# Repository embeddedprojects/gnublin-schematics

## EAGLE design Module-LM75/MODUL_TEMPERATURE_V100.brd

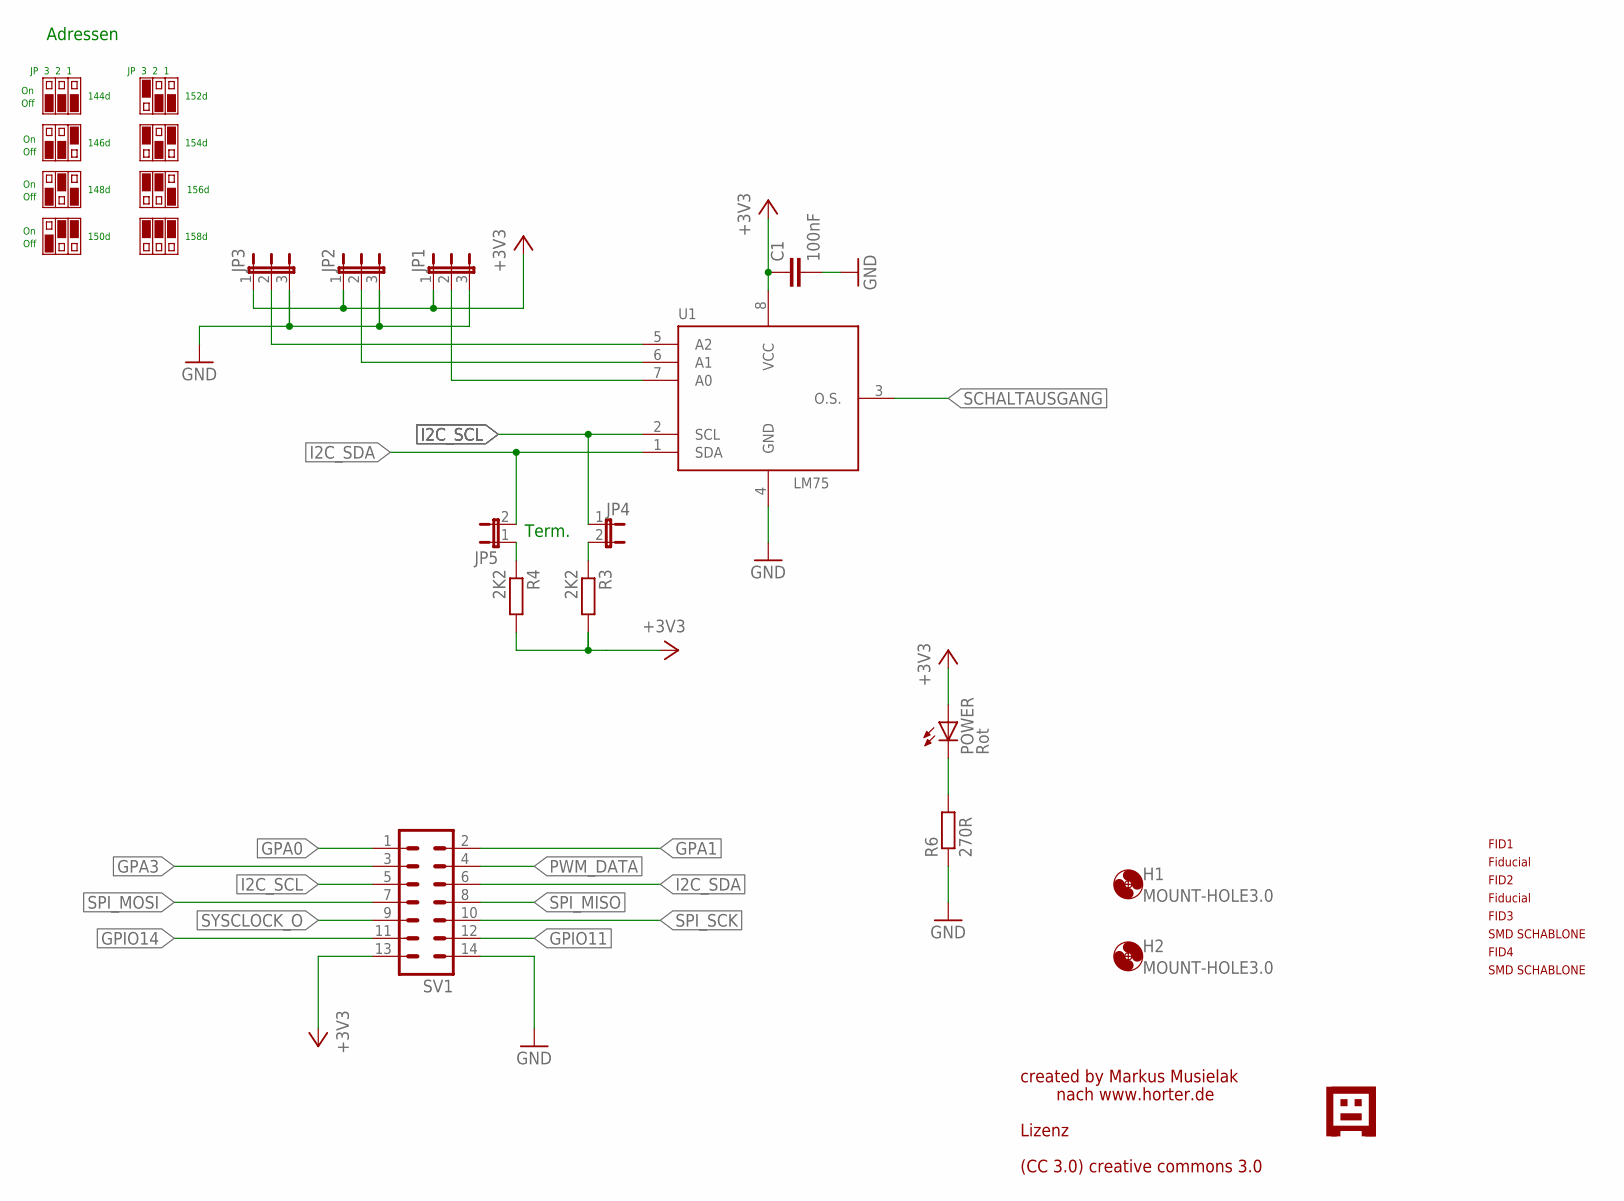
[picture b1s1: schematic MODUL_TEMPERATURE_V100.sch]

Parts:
C1: 100nF; C0805
FID1, FID2, FID3, FID4: PASSERMARKEN_FIDUCIAL
H1, H2: MOUNT-HOLE3.0; 3,0
JP1, JP2, JP3: JP2E; JP2
JP4, JP5: JP1E; JP1
POWER: Rot; CHIP-LED0805
R3, R4: 2K2; R0805
R6: 270R; R0805
SV1: ML14
U1: LM75; SO-8; FARNELL 1699380
U$1: GNUBLINLOGOSIEB; GNUSIEBDRUCK

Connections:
+3V3: C1.1, JP1.1, JP2.1, JP3.1, POWER.A, R3.2, R4.2, SV1.13, U1.8 (VCC)
GND: C1.2, JP1.3, JP2.3, JP3.3, R6.1, SV1.14, U1.4 (GND)
GPA0: SV1.1
GPA1: SV1.2
GPA3: SV1.3
GPIO11: SV1.12
GPIO14: SV1.11
I2C_SCL: JP4.1, SV1.5, U1.2 (SCL)
I2C_SDA: JP5.2, SV1.6, U1.1 (SDA)
unnamed: JP1.2, U1.7 (A0)
unnamed: JP2.2, U1.6 (A1)
unnamed: JP3.2, U1.5 (A2)
unnamed: JP4.2, R3.1
unnamed: JP5.1, R4.1
unnamed: POWER.C, R6.2
PWM_DATA: SV1.4
SCHALTAUSGANG: U1.3 (O.S.)
SPI_MISO: SV1.8
SPI_MOSI: SV1.7
SPI_SCK: SV1.10
SYSCLOCK_O: SV1.9

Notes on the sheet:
Term.
nach www.horter.de
Adressen
JP 3 2 1
Off
144d
146d
148d
150d
152d
154d
156d
158d
created by Markus Musielak
Lizenz
(CC 3.0) creative commons 3.0

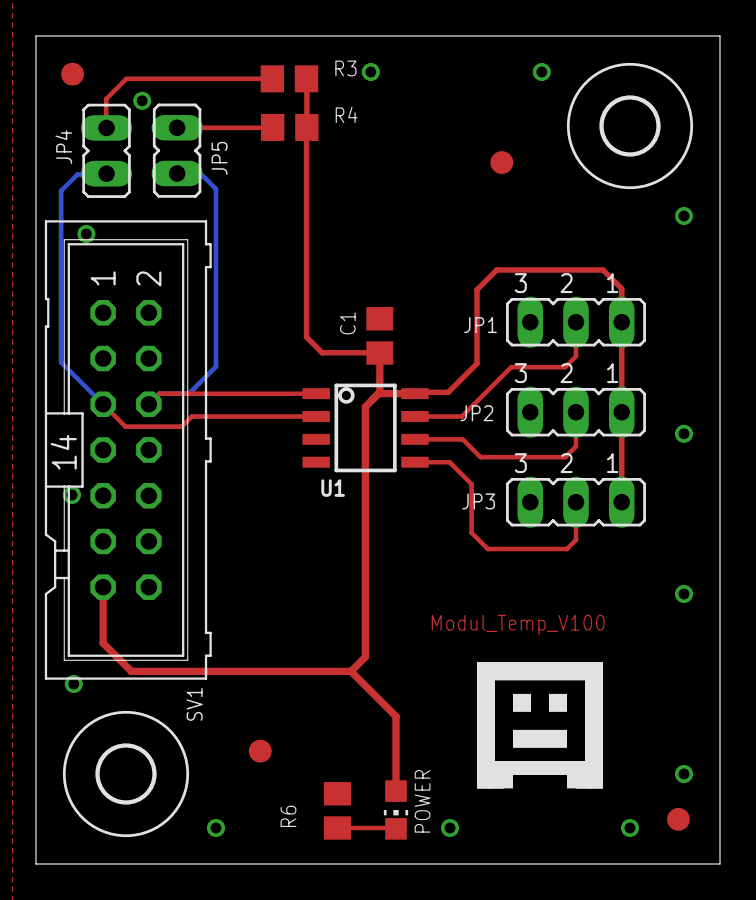
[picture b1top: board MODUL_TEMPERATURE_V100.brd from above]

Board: 2 copper layers, 38.0 x 46.0 mm, 19 parts (0 on the bottom side), 10 nets.

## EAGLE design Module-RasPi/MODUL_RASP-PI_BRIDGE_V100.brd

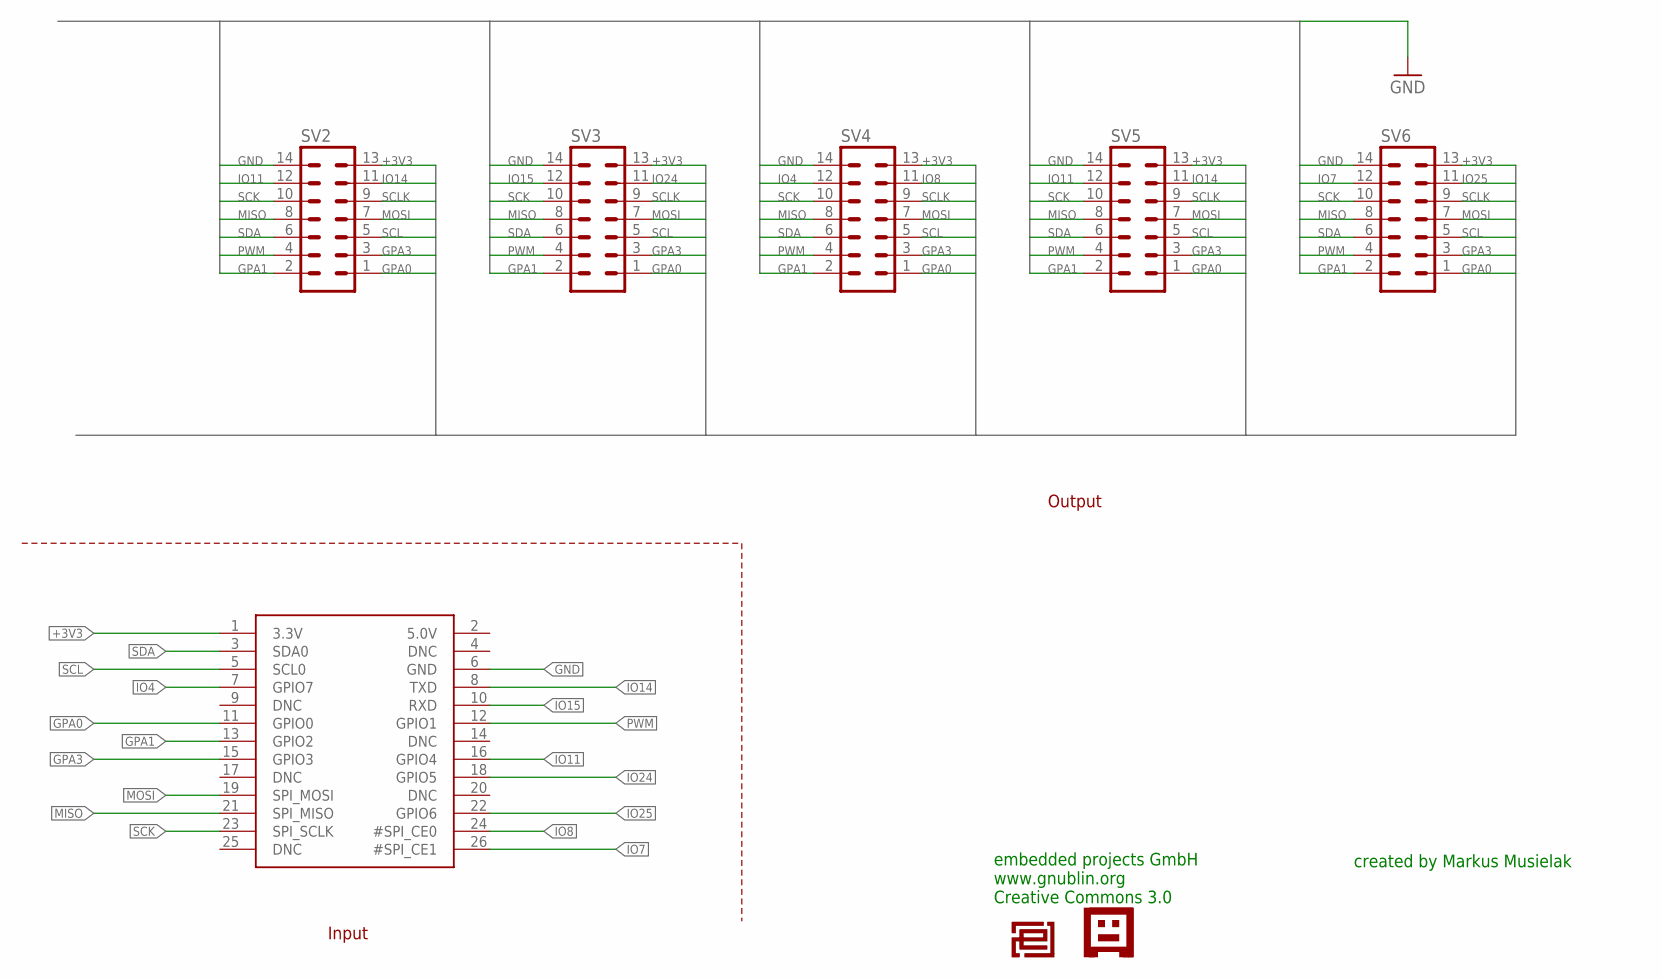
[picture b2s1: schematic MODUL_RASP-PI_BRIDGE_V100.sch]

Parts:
SV2, SV3, SV4, SV5, SV6: ML14
U$1: RASPBERRYPI_BB; RASBERRYPI_SHIELD
U$2: EPLOGOSIEB; EPLOGOSIEBDRUCK
U$4: GNUBLINLOGOSIEB; GNUSIEBDRUCK

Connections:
+3V3: SV2.13, SV3.13, SV4.13, SV5.13, SV6.13, U$1.1 (3.3V)
GND: SV2.14, SV3.14, SV4.14, SV5.14, SV6.14, U$1.6 (GND)
GPA0: SV2.1, SV3.1, SV4.1, SV5.1, SV6.1, U$1.11 (GPIO0)
GPA1: SV2.2, SV3.2, SV4.2, SV5.2, SV6.2, U$1.13 (GPIO2)
GPA3: SV2.3, SV3.3, SV4.3, SV5.3, SV6.3, U$1.15 (GPIO3)
IO4: SV4.12, U$1.7 (GPIO7)
IO7: SV6.12, U$1.26 (#SPI_CE1)
IO8: SV4.11, U$1.24 (#SPI_CE0)
IO11: SV2.12, SV5.12, U$1.16 (GPIO4)
IO14: SV2.11, SV5.11, U$1.8 (TXD)
IO15: SV3.12, U$1.10 (RXD)
IO24: SV3.11, U$1.18 (GPIO5)
IO25: SV6.11, U$1.22 (GPIO6)
MISO: SV2.8, SV3.8, SV4.8, SV5.8, SV6.8, U$1.21 (SPI_MISO)
MOSI: SV2.7, SV3.7, SV4.7, SV5.7, SV6.7, U$1.19 (SPI_MOSI)
PWM: SV2.4, SV3.4, SV4.4, SV5.4, SV6.4, U$1.12 (GPIO1)
SCK: SV2.10, SV3.10, SV4.10, SV5.10, SV6.10, U$1.23 (SPI_SCLK)
SCL: SV2.5, SV3.5, SV4.5, SV5.5, SV6.5, U$1.5 (SCL0)
SCLK: SV2.9, SV3.9, SV4.9, SV5.9, SV6.9
SDA: SV2.6, SV3.6, SV4.6, SV5.6, SV6.6, U$1.3 (SDA0)

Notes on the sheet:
created by Markus Musielak
Input
Output
embedded projects GmbH www.gnublin.org Creative Commons 3.0

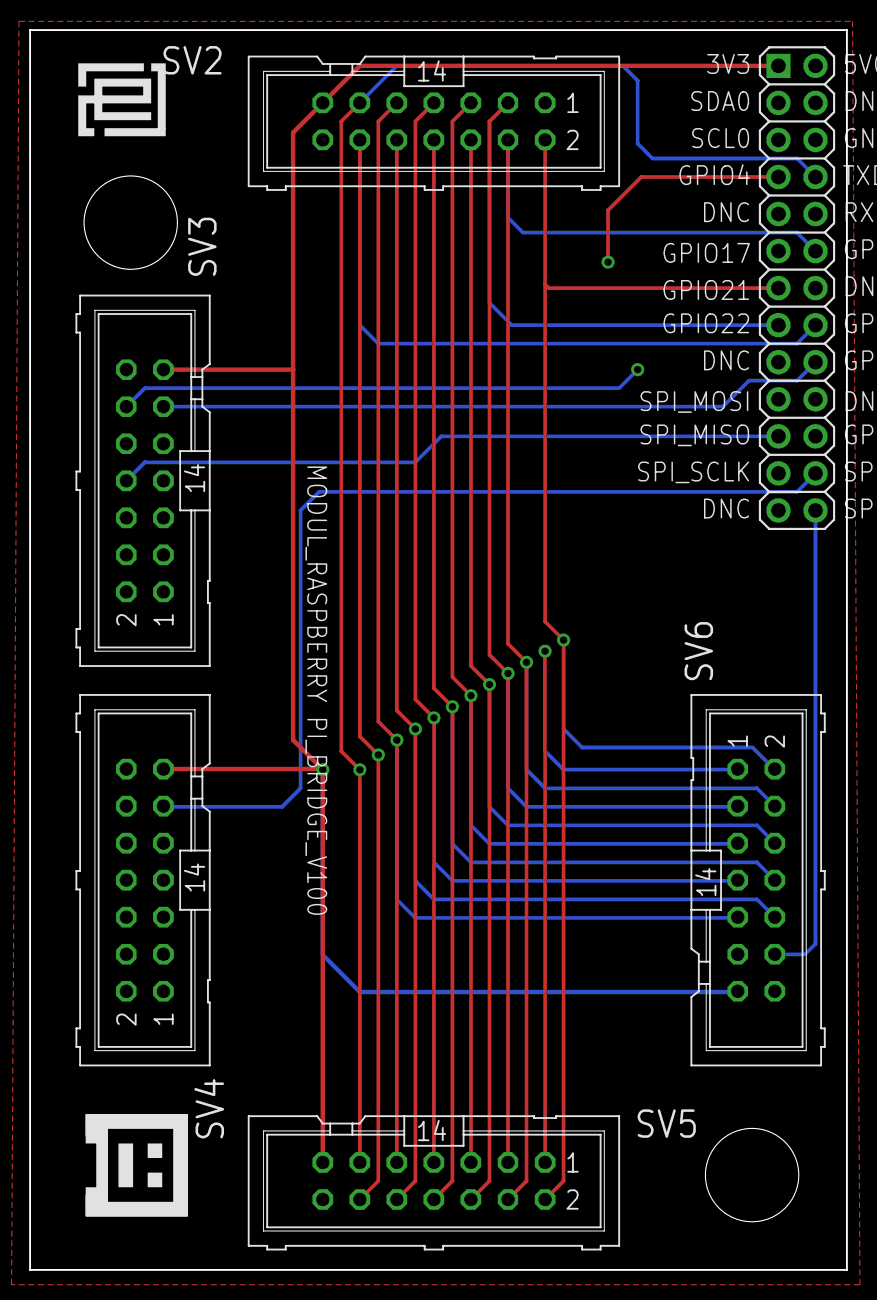
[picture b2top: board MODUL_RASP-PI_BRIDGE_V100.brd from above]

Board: 4 copper layers, 56.0 x 85.0 mm, 8 parts (0 on the bottom side), 20 nets.

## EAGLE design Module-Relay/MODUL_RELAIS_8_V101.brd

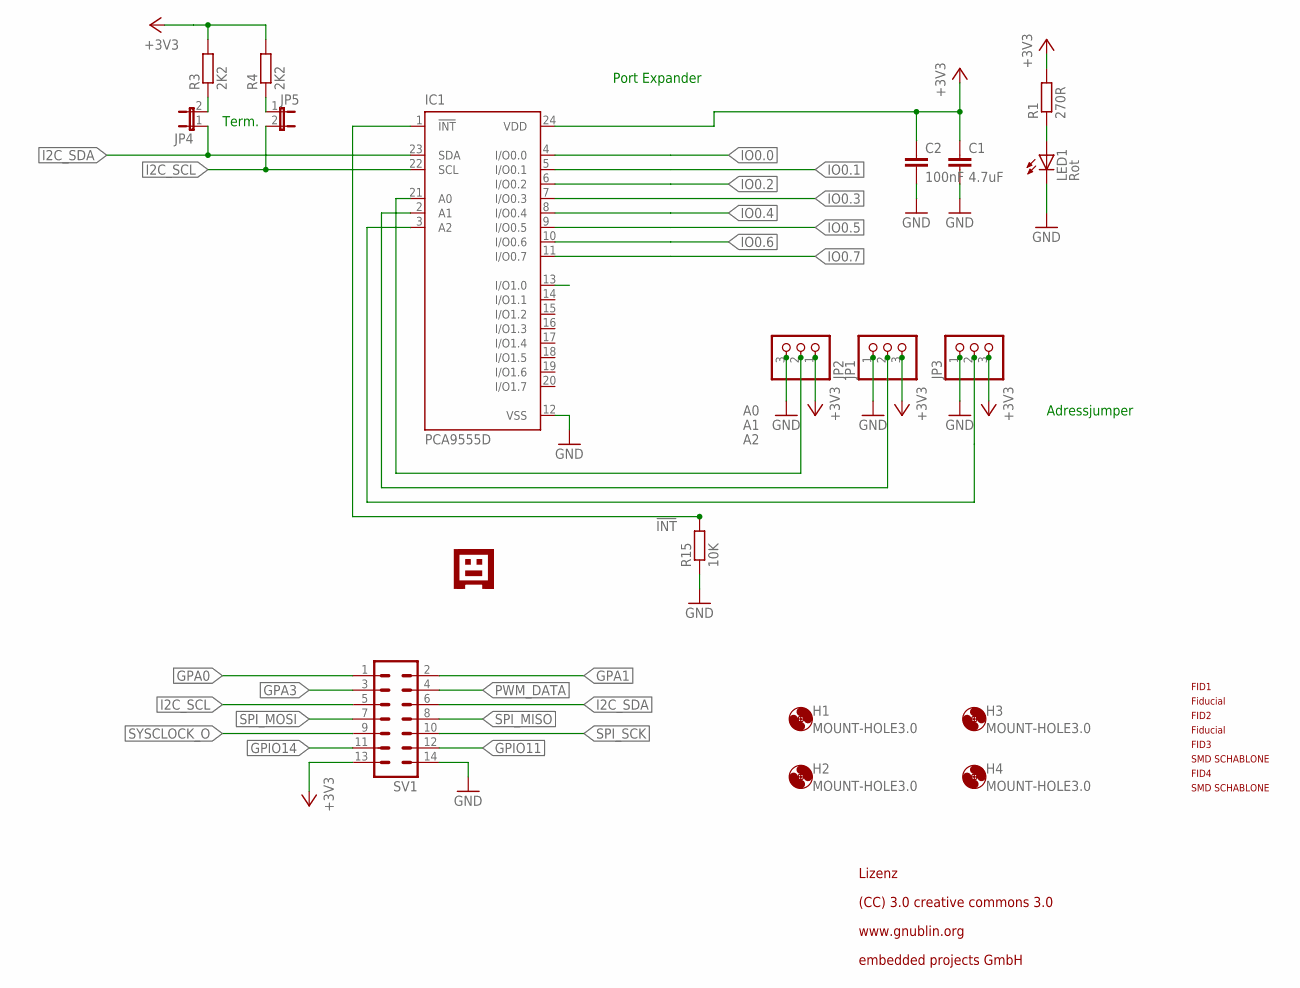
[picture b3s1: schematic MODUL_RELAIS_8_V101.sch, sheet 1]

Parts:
C1: 4.7uF; C0805
C2: 100nF; C0805
FID1, FID2, FID3, FID4: PASSERMARKEN_FIDUCIAL
H1, H2, H3, H4: MOUNT-HOLE3.0; 3,0
IC1: PCA9555D; SO24
JP1, JP2, JP3: PINHD-1X3; 1X03
JP4, JP5: JP1E; JP1
LED1: Rot; CHIP-LED0805
R1: 270R; R0805
R3, R4: 2K2; R0805
R15: 10K; R0805
SV1: ML14
U$1: GNUBLINLOGOSIEB; GNUSIEBDRUCK

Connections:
!INT: IC1.1 (!INT), R15.2
+3V3: C1.1, C2.1, IC1.24 (VDD), JP1.3, JP2.1, JP3.3, R1.2, R3.2, R4.2, SV1.13; also elsewhere on the board
A0: IC1.21 (A0), JP2.2
A1: IC1.2 (A1), JP1.2
A2: IC1.3 (A2), JP3.2
GND: C1.2, C2.2, IC1.12 (VSS), JP1.1, JP2.3, JP3.1, LED1.C, R15.1, SV1.14; also elsewhere on the board
GPA0: SV1.1
GPA1: SV1.2
GPA3: SV1.3
GPIO11: SV1.12
GPIO14: SV1.11
I2C_SCL: IC1.22 (SCL), JP5.2, SV1.5
I2C_SDA: IC1.23 (SDA), JP4.1, SV1.6
IO0.0: IC1.4 (I/O0.0); also elsewhere on the board
IO0.1: IC1.5 (I/O0.1); also elsewhere on the board
IO0.2: IC1.6 (I/O0.2); also elsewhere on the board
IO0.3: IC1.7 (I/O0.3); also elsewhere on the board
IO0.4: IC1.8 (I/O0.4); also elsewhere on the board
IO0.5: IC1.9 (I/O0.5); also elsewhere on the board
IO0.6: IC1.10 (I/O0.6); also elsewhere on the board
IO0.7: IC1.11 (I/O0.7); also elsewhere on the board
IO1.0: IC1.13 (I/O1.0)
unnamed: JP4.2, R3.1
unnamed: LED1.A, R1.1
unnamed: JP5.1, R4.1
PWM_DATA: SV1.4
SPI_MISO: SV1.8
SPI_MOSI: SV1.7
SPI_SCK: SV1.10
SYSCLOCK_O: SV1.9

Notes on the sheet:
Port Expander
Adressjumper
Term.
(CC) 3.0 creative commons 3.0
Lizenz
www.gnublin.org
embedded projects GmbH

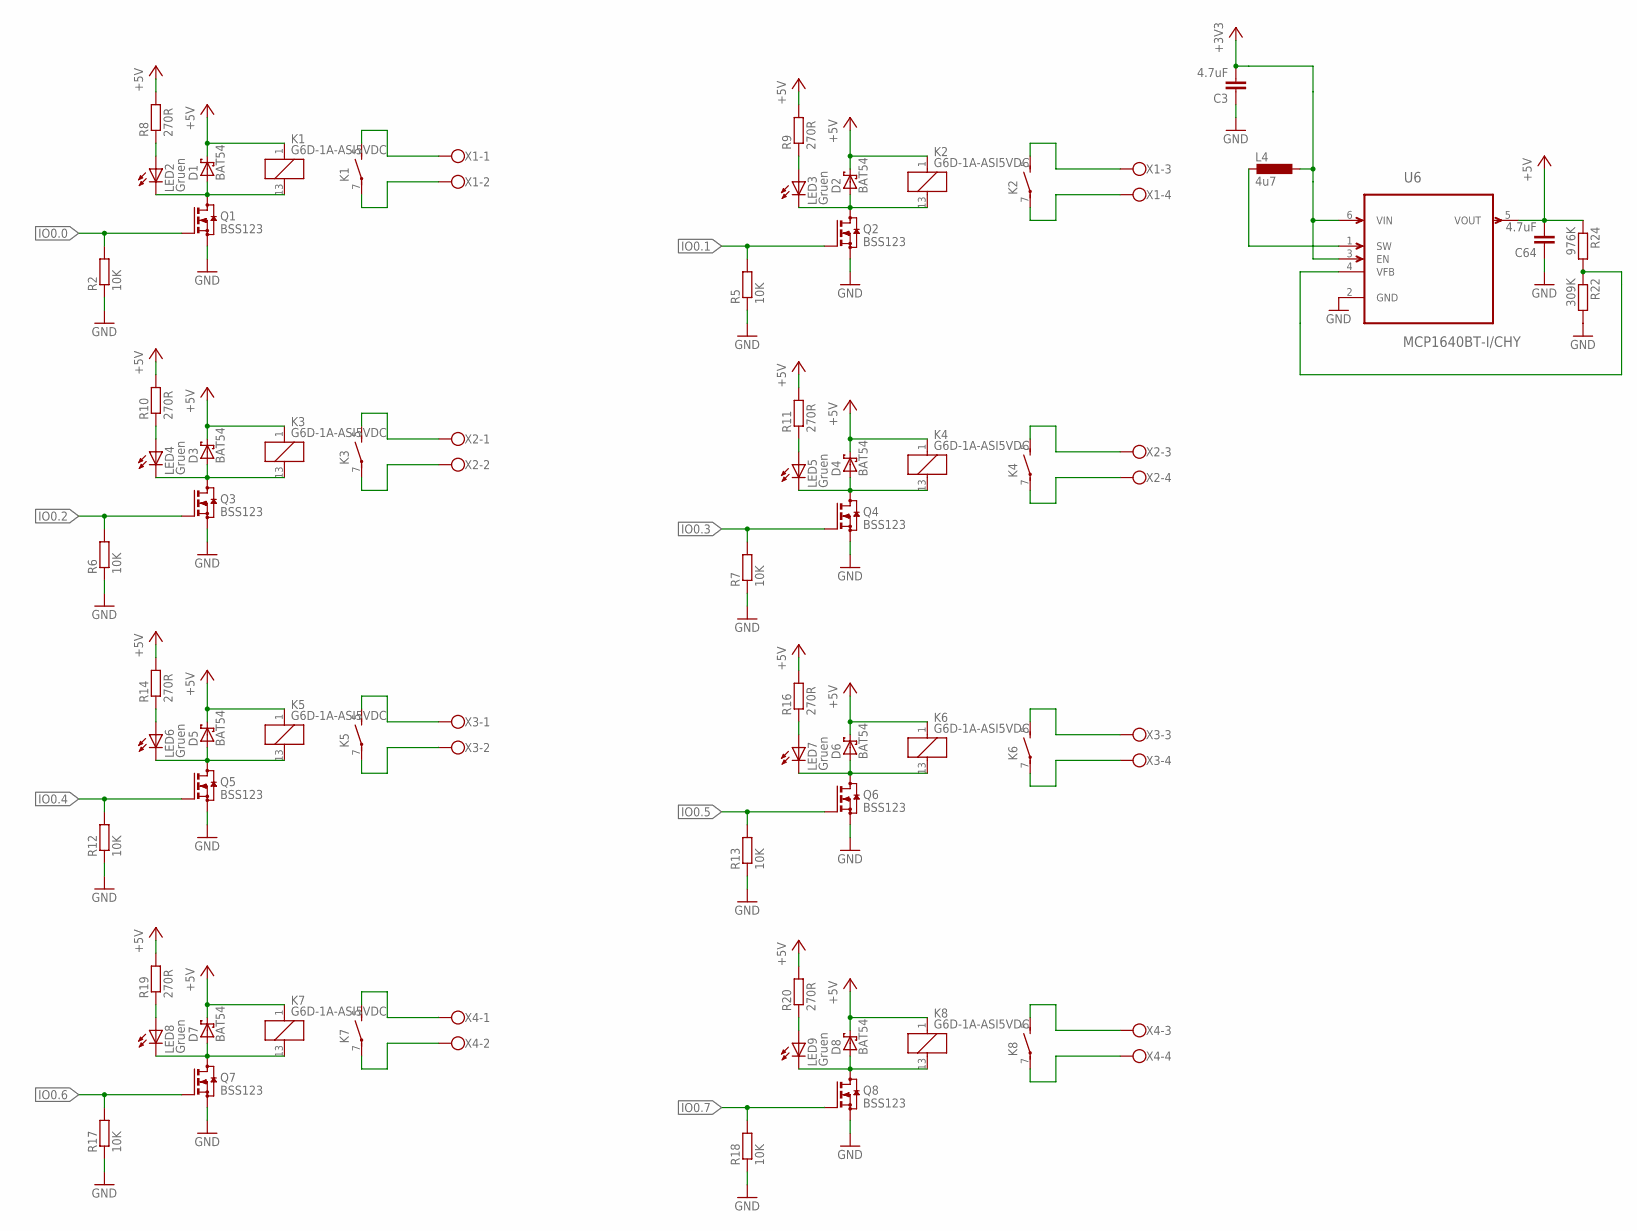
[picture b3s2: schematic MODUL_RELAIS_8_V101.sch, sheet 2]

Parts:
C3, C64: 4.7uF; C0805
D1, D2, D3, D4, D5, D6, D7, D8: BAT54; DIODE_SOT23
K1, K2, K3, K4, K5, K6, K7, K8: G6D-1A-ASI5VDC; RELAY_G6D
L4: 4u7; PSU3014
LED2, LED3, LED4, LED5, LED6, LED7, LED8, LED9: Gruen; CHIP-LED0805
Q1, Q2, Q3, Q4, Q5, Q6, Q7, Q8: BSS123; TRANSISTOR-SMALL-SIGNAL_SOT23
R2, R5, R6, R7, R12, R13, R17, R18: 10K; R0805
R8, R9, R10, R11, R14, R16, R19, R20: 270R; R0805
R22: 309K; R0805
R24: 976K; R0805
U6: MCP1640BT-I/CHY; SOT95P270X145-6N
X1, X2, X3, X4: W237-04P; W237-4P

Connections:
+3V3: C3.2, L4.2, U6.3 (EN), U6.6 (VIN); also elsewhere on the board
+5V: C64.2, D1.3 (C), D2.3 (C), D3.3 (C), D4.3 (C), D5.3 (C), D6.3 (C), D7.3 (C), D8.3 (C), K1.1, K2.1, K3.1, K4.1, K5.1, K6.1, K7.1, K8.1, R8.2, R9.2, R10.2, R11.2, R14.2, R16.2, R19.2, R20.2, R24.1, U6.5 (VOUT)
ENABLE_5V: L4.1, U6.1 (SW)
GND: C3.1, C64.1, Q1.2 (S), Q2.2 (S), Q3.2 (S), Q4.2 (S), Q5.2 (S), Q6.2 (S), Q7.2 (S), Q8.2 (S), R2.1, R5.1, R6.1, R7.1, R12.1, R13.1, R17.1, R18.1, R22.2, U6.2 (GND); also elsewhere on the board
IO0.0: Q1.1 (G), R2.2; also elsewhere on the board
IO0.1: Q2.1 (G), R5.2; also elsewhere on the board
IO0.2: Q3.1 (G), R6.2; also elsewhere on the board
IO0.3: Q4.1 (G), R7.2; also elsewhere on the board
IO0.4: Q5.1 (G), R12.2; also elsewhere on the board
IO0.5: Q6.1 (G), R13.2; also elsewhere on the board
IO0.6: Q7.1 (G), R17.2; also elsewhere on the board
IO0.7: Q8.1 (G), R18.2; also elsewhere on the board
unnamed: D1.1 (A), K1.13 (2), LED2.C, Q1.3 (D)
unnamed: LED2.A, R8.1
unnamed: D2.1 (A), K2.13 (2), LED3.C, Q2.3 (D)
unnamed: LED3.A, R9.1
unnamed: K1.5 (S), X1.1
unnamed: K1.7, X1.2
unnamed: K2.5 (S), X1.3
unnamed: K2.7, X1.4
unnamed: D3.1 (A), K3.13 (2), LED4.C, Q3.3 (D)
unnamed: D4.1 (A), K4.13 (2), LED5.C, Q4.3 (D)
unnamed: LED4.A, R10.1
unnamed: LED5.A, R11.1
unnamed: K3.5 (S), X2.1
unnamed: K3.7, X2.2
unnamed: K4.5 (S), X2.3
unnamed: K4.7, X2.4
unnamed: D5.1 (A), K5.13 (2), LED6.C, Q5.3 (D)
unnamed: D6.1 (A), K6.13 (2), LED7.C, Q6.3 (D)
unnamed: LED6.A, R14.1
unnamed: LED7.A, R16.1
unnamed: K5.5 (S), X3.1
unnamed: K5.7, X3.2
unnamed: K6.5 (S), X3.3
unnamed: K6.7, X3.4
unnamed: D7.1 (A), K7.13 (2), LED8.C, Q7.3 (D)
unnamed: D8.1 (A), K8.13 (2), LED9.C, Q8.3 (D)
unnamed: LED8.A, R19.1
unnamed: LED9.A, R20.1
unnamed: K7.5 (S), X4.1
unnamed: K7.7, X4.2
unnamed: K8.5 (S), X4.3
unnamed: K8.7, X4.4
unnamed: R22.1, R24.2, U6.4 (VFB)

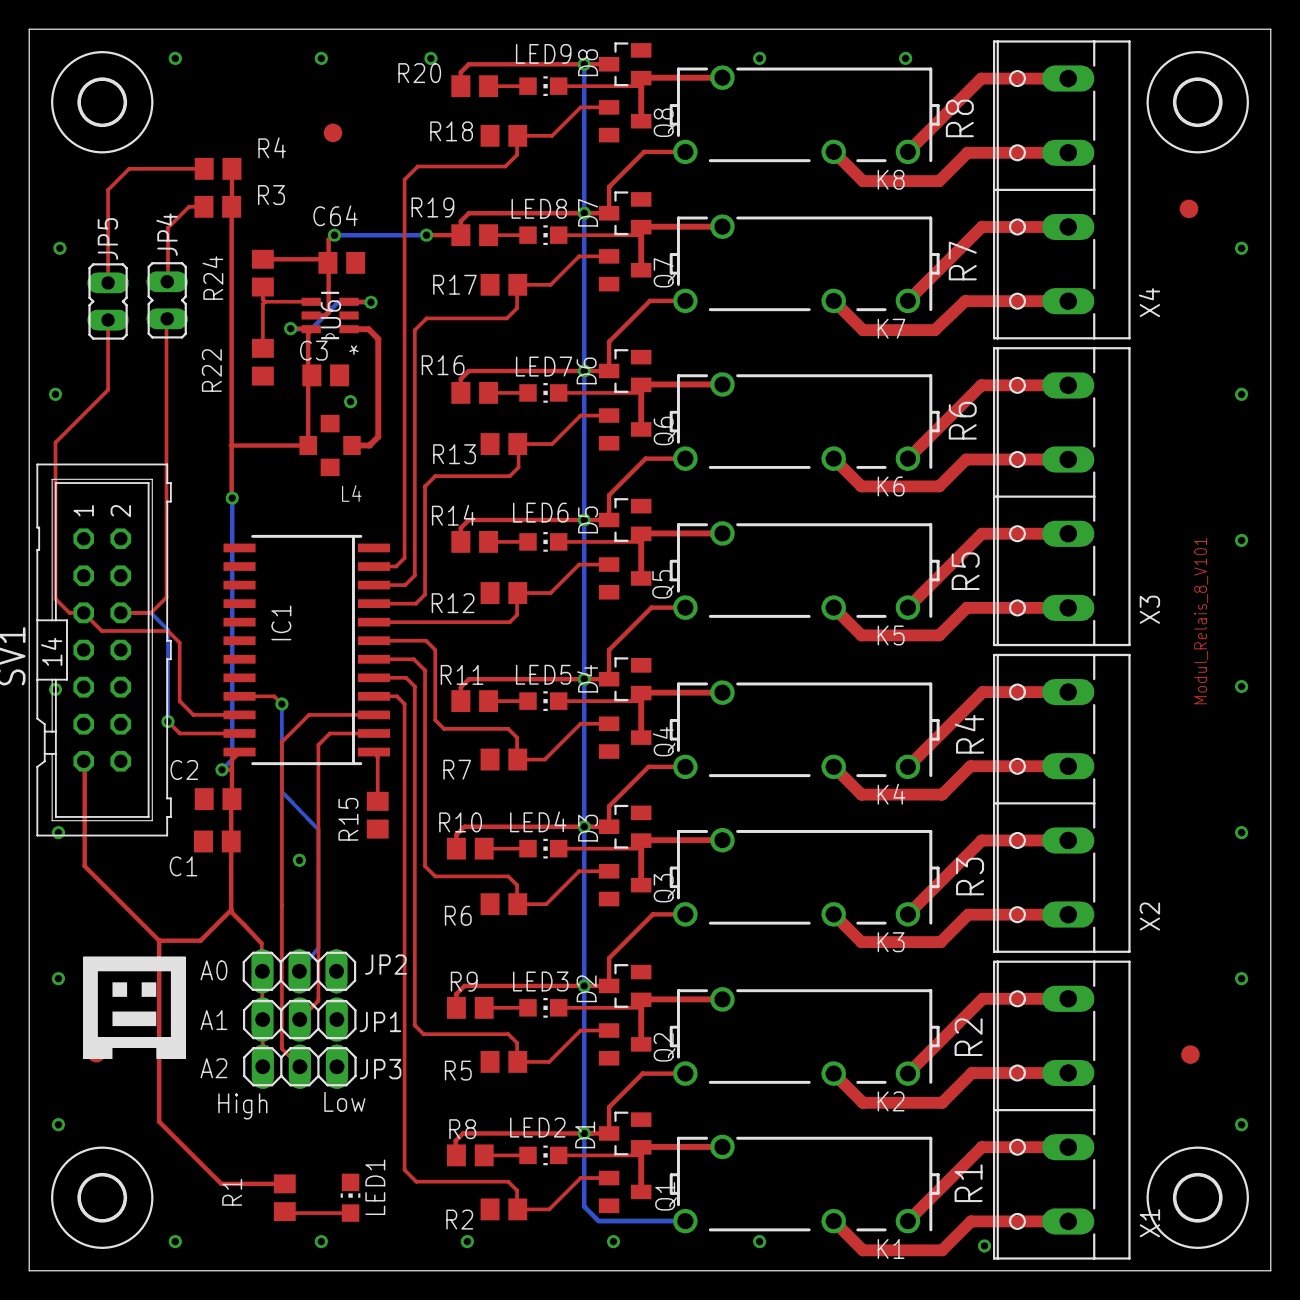
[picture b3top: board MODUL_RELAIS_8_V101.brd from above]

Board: 2 copper layers, 85.0 x 85.0 mm, 81 parts (0 on the bottom side), 54 nets.

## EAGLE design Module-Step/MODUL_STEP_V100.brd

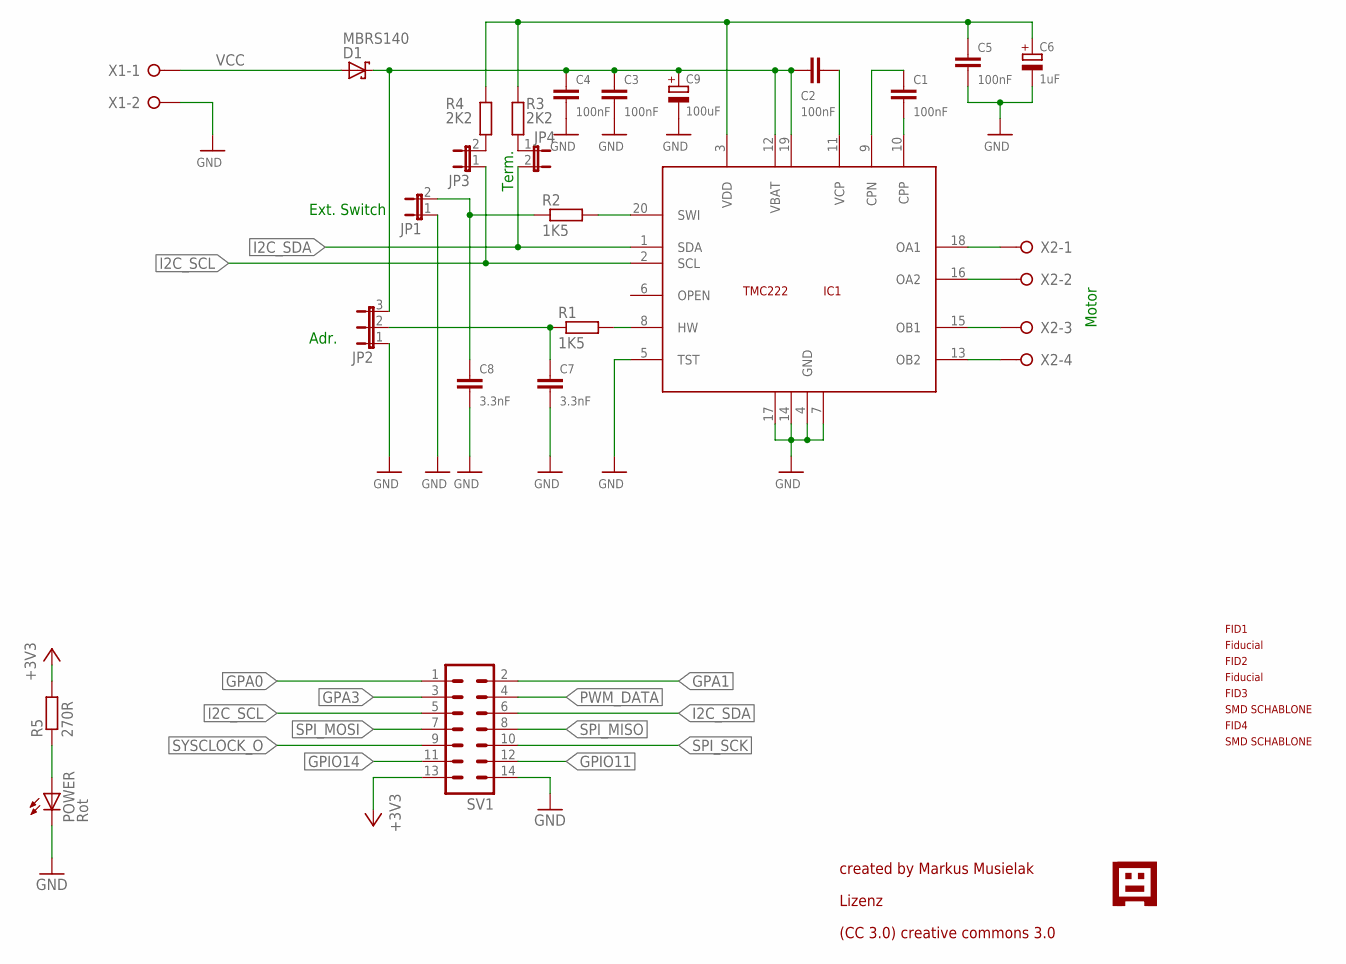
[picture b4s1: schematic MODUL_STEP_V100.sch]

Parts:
C1, C2, C3, C4, C5: 100nF; C0805
C6: 1uF; B/3528-21R
C7, C8: 3.3nF; C0805
C9: 100uF; E5-10,5
D1: MBRS140; SMB
FID1, FID2, FID3, FID4: PASSERMARKEN_FIDUCIAL
IC1: TMC222; SOIC20; FARNELL 1214195
JP1, JP3, JP4: JP1E; JP1
JP2: JP2E; JP2
POWER: Rot; CHIP-LED0805
R1, R2: 1K5; R0805
R3, R4: 2K2; R0805
R5: 270R; R0805
SV1: ML14
U$1: GNUBLINLOGOSIEB; GNUSIEBDRUCK
X1: W237-02P; W237-132
X2: W237-04P; W237-4P

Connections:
+3V3: R5.2, SV1.13
GND: C3.2, C4.2, C5.2, C6.-, C7.2, C8.2, C9.-, IC1.4 (GND), IC1.5 (TST), IC1.7 (GND2), IC1.14 (GND3), IC1.17 (GND4), JP1.1, JP2.1, POWER.C, SV1.14, X1.2
GPA0: SV1.1
GPA1: SV1.2
GPA3: SV1.3
GPIO11: SV1.12
GPIO14: SV1.11
I2C_SCL: IC1.2 (SCL), JP3.1, SV1.5
I2C_SDA: IC1.1 (SDA), JP4.2, SV1.6
unnamed: POWER.A, R5.1
unnamed: C1.1, IC1.9 (CPN)
unnamed: C1.2, IC1.10 (CPP)
unnamed: C2.2, IC1.11 (VCP)
unnamed: C2.1, C3.1, C4.1, C9.+, D1.C, IC1.12 (VBAT), IC1.19 (VBAT2), JP2.3
unnamed: IC1.8 (HW), R1.2
unnamed: C7.1, JP2.2, R1.1
unnamed: C8.1, JP1.2, R2.1
unnamed: IC1.20 (SWI), R2.2
unnamed: IC1.13 (OB2), X2.4
unnamed: IC1.15 (OB1), X2.3
unnamed: IC1.16 (OA2), X2.2
unnamed: IC1.18 (OA1), X2.1
unnamed: JP3.2, R4.1
unnamed: JP4.1, R3.1
unnamed: C5.1, C6.+, IC1.3 (VDD), R3.2, R4.2
PWM_DATA: SV1.4
SPI_MISO: SV1.8
SPI_MOSI: SV1.7
SPI_SCK: SV1.10
SYSCLOCK_O: SV1.9
VCC: D1.A, X1.1

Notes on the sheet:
created by Markus Musielak
Adr.
Ext. Switch
Term.
Motor
Lizenz
(CC 3.0) creative commons 3.0

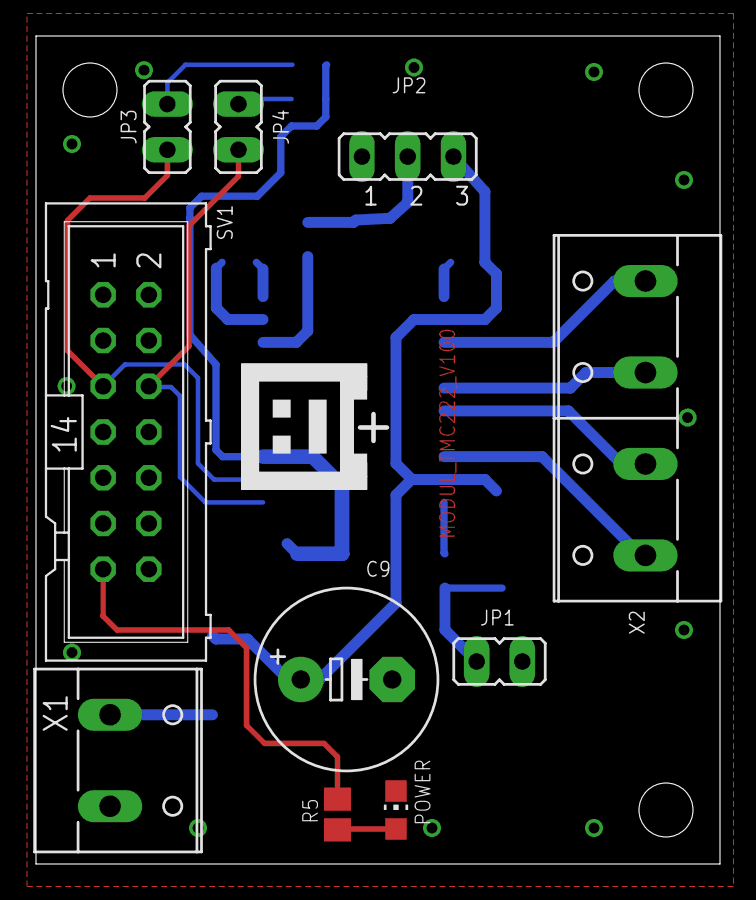
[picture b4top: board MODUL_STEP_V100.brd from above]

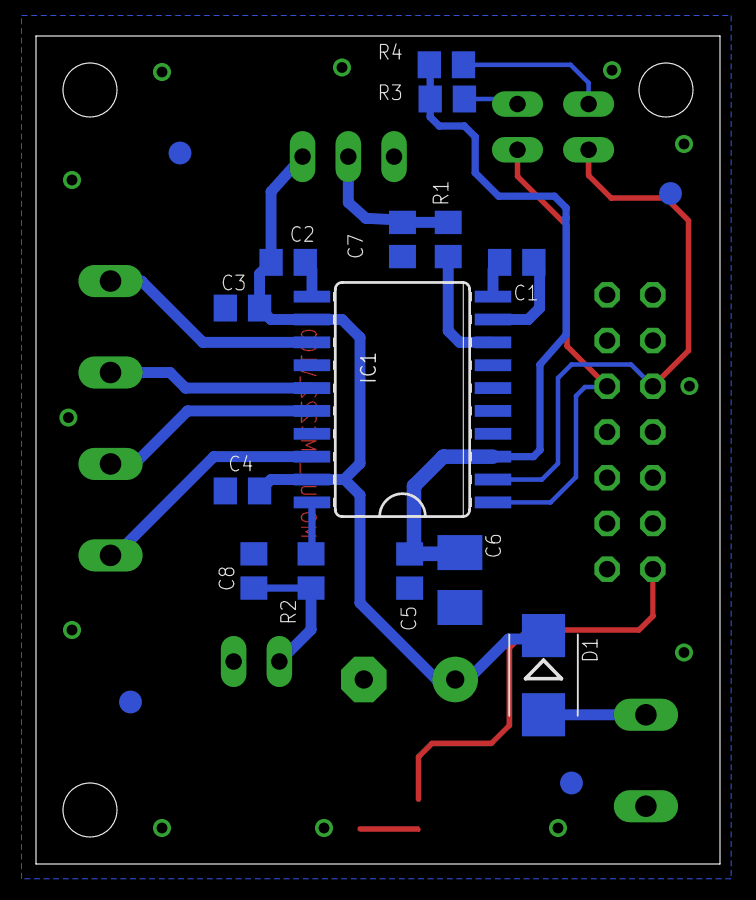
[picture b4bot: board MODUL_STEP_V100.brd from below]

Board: 2 copper layers, 38.0 x 46.0 mm, 29 parts (18 on the bottom side), 21 nets.

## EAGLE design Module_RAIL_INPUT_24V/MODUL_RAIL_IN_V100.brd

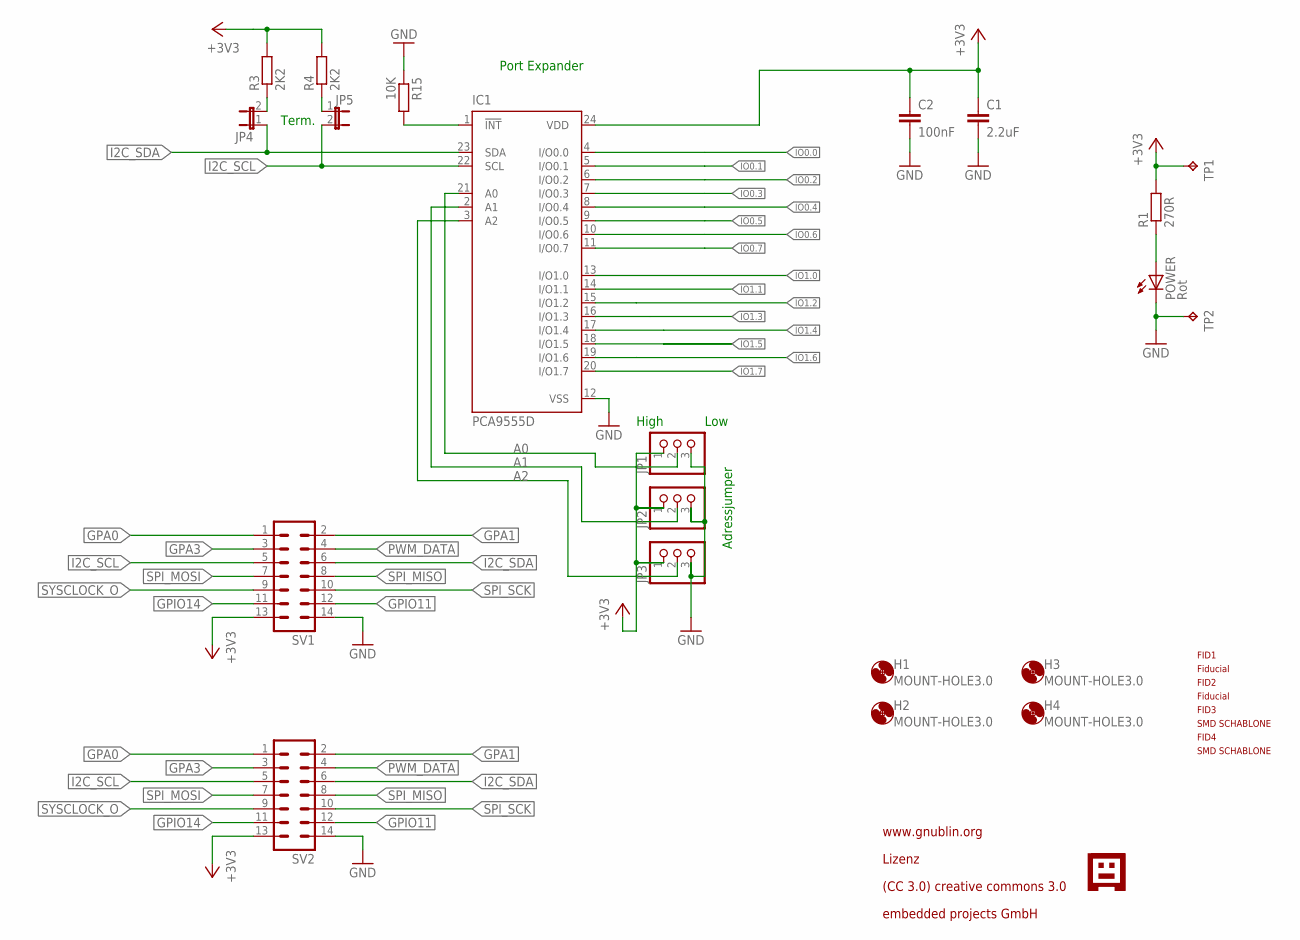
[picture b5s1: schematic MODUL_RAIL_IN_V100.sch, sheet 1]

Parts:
C1: 2.2uF; C0805
C2: 100nF; C0805
FID1, FID2, FID3, FID4: PASSERMARKEN_FIDUCIAL
H1, H2, H3, H4: MOUNT-HOLE3.0; 3,0
IC1: PCA9555D; SO24
JP1, JP2, JP3: PINHD-1X3; 1X03
JP4, JP5: JP1E; JP1
POWER: Rot; CHIP-LED0805
R1: 270R; R0805
R3, R4: 2K2; R0805
R15: 10K; R0805
SV1, SV2: ML14
TP1, TP2: TPB1,27; B1,27
U$2: GNUBLINLOGOSIEB; GNUSIEBDRUCK

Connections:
!INT: IC1.1 (!INT), R15.2
+3V3: C1.1, C2.1, IC1.24 (VDD), JP1.1, JP2.1, JP3.1, R1.2, R3.2, R4.2, SV1.13, SV2.13, TP1.TP; also elsewhere on the board
A0: IC1.21 (A0), JP1.2
A1: IC1.2 (A1), JP2.2
A2: IC1.3 (A2), JP3.2
GND: C1.2, C2.2, IC1.12 (VSS), JP1.3, JP2.3, JP3.3, POWER.C, R15.1, SV1.14, SV2.14, TP2.TP; also elsewhere on the board
GPA0: SV1.1, SV2.1
GPA1: SV1.2, SV2.2
GPA3: SV1.3, SV2.3
GPIO11: SV1.12, SV2.12
GPIO14: SV1.11, SV2.11
I2C_SCL: IC1.22 (SCL), JP5.2, SV1.5, SV2.5
I2C_SDA: IC1.23 (SDA), JP4.1, SV1.6, SV2.6
IO0.0: IC1.4 (I/O0.0)
IO0.1: IC1.5 (I/O0.1)
IO0.2: IC1.6 (I/O0.2)
IO0.3: IC1.7 (I/O0.3)
IO0.4: IC1.8 (I/O0.4)
IO0.5: IC1.9 (I/O0.5)
IO0.6: IC1.10 (I/O0.6)
IO0.7: IC1.11 (I/O0.7)
IO1.0: IC1.13 (I/O1.0); also elsewhere on the board
IO1.1: IC1.14 (I/O1.1); also elsewhere on the board
IO1.2: IC1.15 (I/O1.2); also elsewhere on the board
IO1.3: IC1.16 (I/O1.3); also elsewhere on the board
IO1.4: IC1.17 (I/O1.4)
IO1.5: IC1.18 (I/O1.5)
IO1.6: IC1.19 (I/O1.6)
IO1.7: IC1.20 (I/O1.7)
unnamed: JP4.2, R3.1
unnamed: POWER.A, R1.1
unnamed: JP5.1, R4.1
PWM_DATA: SV1.4, SV2.4
SPI_MISO: SV1.8, SV2.8
SPI_MOSI: SV1.7, SV2.7
SPI_SCK: SV1.10, SV2.10
SYSCLOCK_O: SV1.9, SV2.9

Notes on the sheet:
Port Expander
Adressjumper
Term.
High
Low
www.gnublin.org
Lizenz
(CC 3.0) creative commons 3.0
embedded projects GmbH

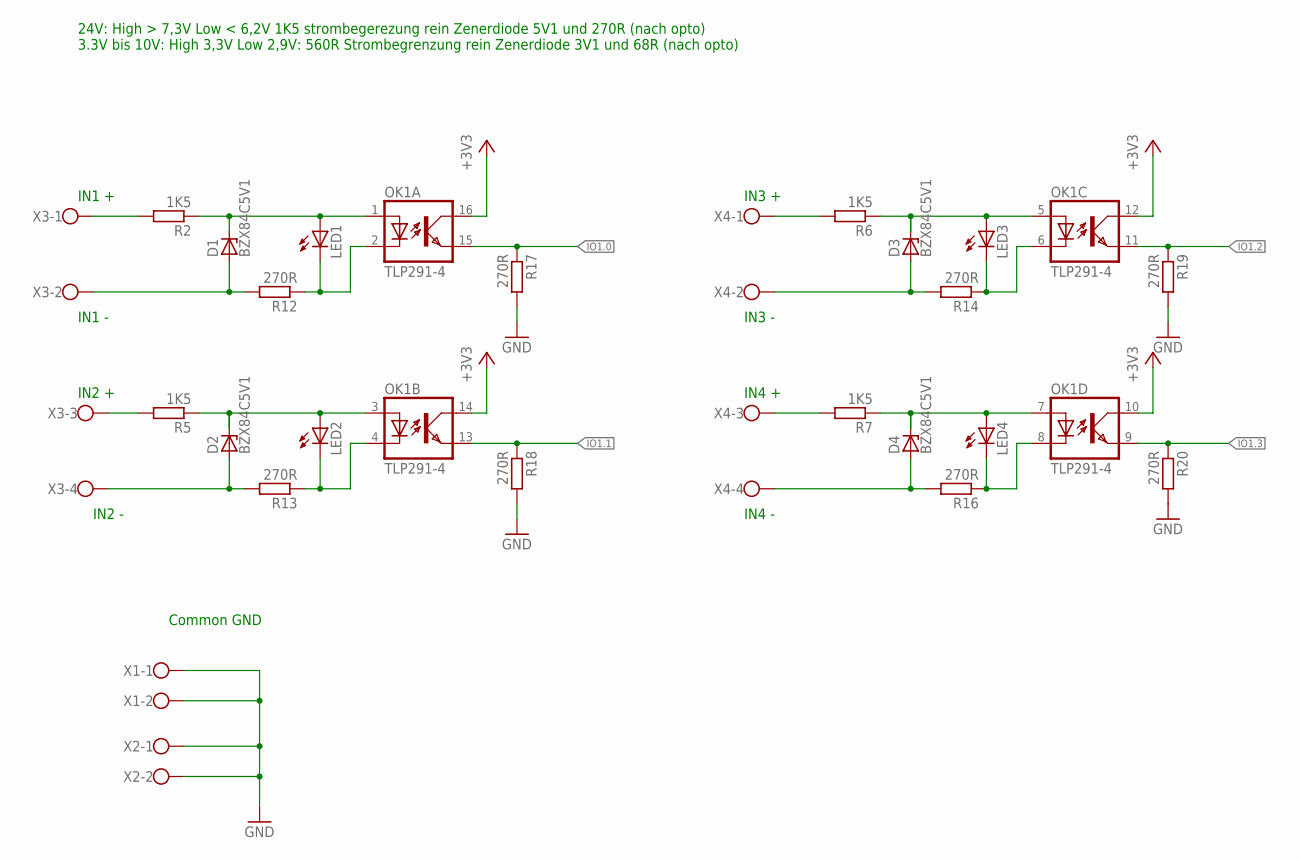
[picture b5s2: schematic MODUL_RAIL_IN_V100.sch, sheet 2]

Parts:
D1: BZX84C5V1; TO236; FARNELL 1081430
D2, D3, D4: BZX84C5V1; TO236
LED1, LED2, LED3, LED4: LEDCHIPLED_0805; CHIPLED_0805
OK1: TLP291-4; MINI-FLAT-16
R2, R5, R6, R7: 1K5; R0805
R12, R13, R14, R16, R17, R18, R19, R20: 270R; R0805
X1, X2: W237-02P; W237-132
X3, X4: W237-04P; W237-4P

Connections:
+3V3: OK1.10 (COL), OK1.12 (COL), OK1.14 (COL), OK1.16 (COL); also elsewhere on the board
GND: R17.2, R18.2, R19.2, R20.2, X1.1, X1.2, X2.1, X2.2; also elsewhere on the board
IO1.0: OK1.15 (EMIT), R17.1; also elsewhere on the board
IO1.1: OK1.13 (EMIT), R18.1; also elsewhere on the board
IO1.2: OK1.11 (EMIT), R19.1; also elsewhere on the board
IO1.3: OK1.9 (EMIT), R20.1; also elsewhere on the board
unnamed: R2.2, X3.1
unnamed: D1.C, LED1.A, OK1.1 (A), R2.1
unnamed: LED1.C, OK1.2 (C), R12.1
unnamed: R5.2, X3.3
unnamed: D2.C, LED2.A, OK1.3 (A), R5.1
unnamed: LED2.C, OK1.4 (C), R13.1
unnamed: D1.A, R12.2, X3.2
unnamed: R6.2, X4.1
unnamed: D3.C, LED3.A, OK1.5 (A), R6.1
unnamed: R7.2, X4.3
unnamed: D4.C, LED4.A, OK1.7 (A), R7.1
unnamed: LED3.C, OK1.6 (C), R14.1
unnamed: D2.A, R13.2, X3.4
unnamed: LED4.C, OK1.8 (C), R16.1
unnamed: D3.A, R14.2, X4.2
unnamed: D4.A, R16.2, X4.4

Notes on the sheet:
IN1 +
IN1 -
IN2 +
IN2 -
IN3 +
IN3 -
IN4 +
IN4 -
Common GND
24V: High > 7,3V Low < 6,2V 1K5 strombegerezung rein Zenerdiode 5V1 und 270R (nach opto) 3.3V bis 10V: High 3,3V Low 2,9V: 560R Strombegrenzung rein Zenerdiode 3V1 und 68R (nach opto)
